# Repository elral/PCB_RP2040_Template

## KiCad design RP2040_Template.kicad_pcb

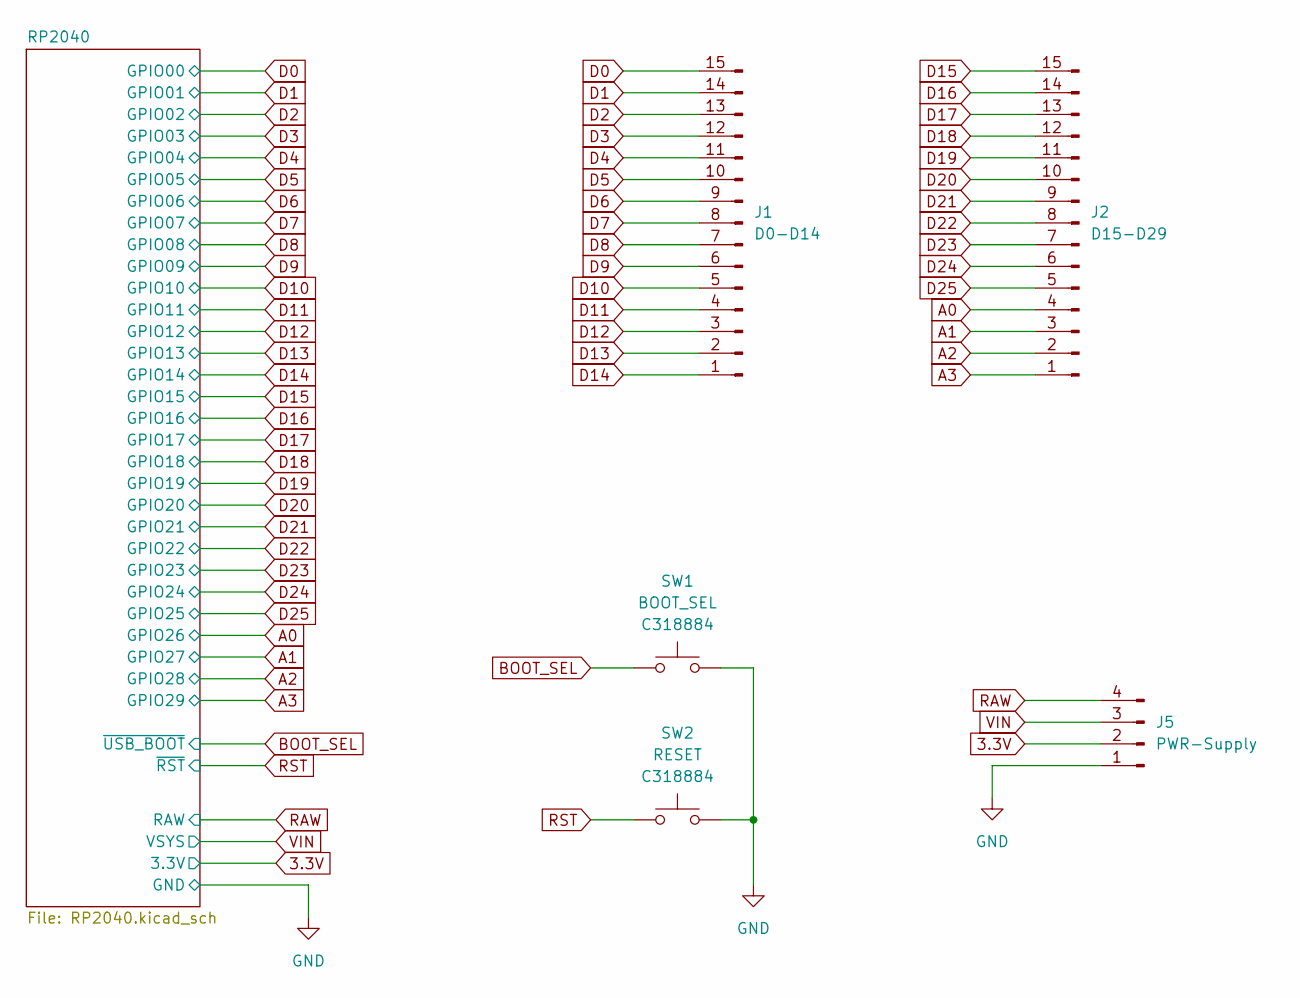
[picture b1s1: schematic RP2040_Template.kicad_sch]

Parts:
J1: D0-D14; PinHeader_1x15_P2.54mm_Vertical
J2: D15-D29; PinHeader_1x15_P2.54mm_Vertical
J5: PWR-Supply; PinHeader_1x04_P2.54mm_Vertical
SW1: BOOT_SEL; SW_Push_1P1T_XKB_TS-1187A; JLCPCB C318884
SW2: RESET; SW_Push_1P1T_XKB_TS-1187A; JLCPCB C318884

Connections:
3.3V: J5.2; also elsewhere on the board
A0: J2.4; also elsewhere on the board
A1: J2.3; also elsewhere on the board
A2: J2.2; also elsewhere on the board
A3: J2.1; also elsewhere on the board
BOOT_SEL: SW1.1; also elsewhere on the board
D0: J1.15; also elsewhere on the board
D1: J1.14; also elsewhere on the board
D2: J1.13; also elsewhere on the board
D3: J1.12; also elsewhere on the board
D4: J1.11; also elsewhere on the board
D5: J1.10; also elsewhere on the board
D6: J1.9; also elsewhere on the board
D7: J1.8; also elsewhere on the board
D8: J1.7; also elsewhere on the board
D9: J1.6; also elsewhere on the board
D10: J1.5; also elsewhere on the board
D11: J1.4; also elsewhere on the board
D12: J1.3; also elsewhere on the board
D13: J1.2; also elsewhere on the board
D14: J1.1; also elsewhere on the board
D15: J2.15; also elsewhere on the board
D16: J2.14; also elsewhere on the board
D17: J2.13; also elsewhere on the board
D18: J2.12; also elsewhere on the board
D19: J2.11; also elsewhere on the board
D20: J2.10; also elsewhere on the board
D21: J2.9; also elsewhere on the board
D22: J2.8; also elsewhere on the board
D23: J2.7; also elsewhere on the board
D24: J2.6; also elsewhere on the board
D25: J2.5; also elsewhere on the board
GND: J5.1, SW1.2, SW2.2; also elsewhere on the board
RAW: J5.4; also elsewhere on the board
RST: SW2.1; also elsewhere on the board
VIN: J5.3; also elsewhere on the board

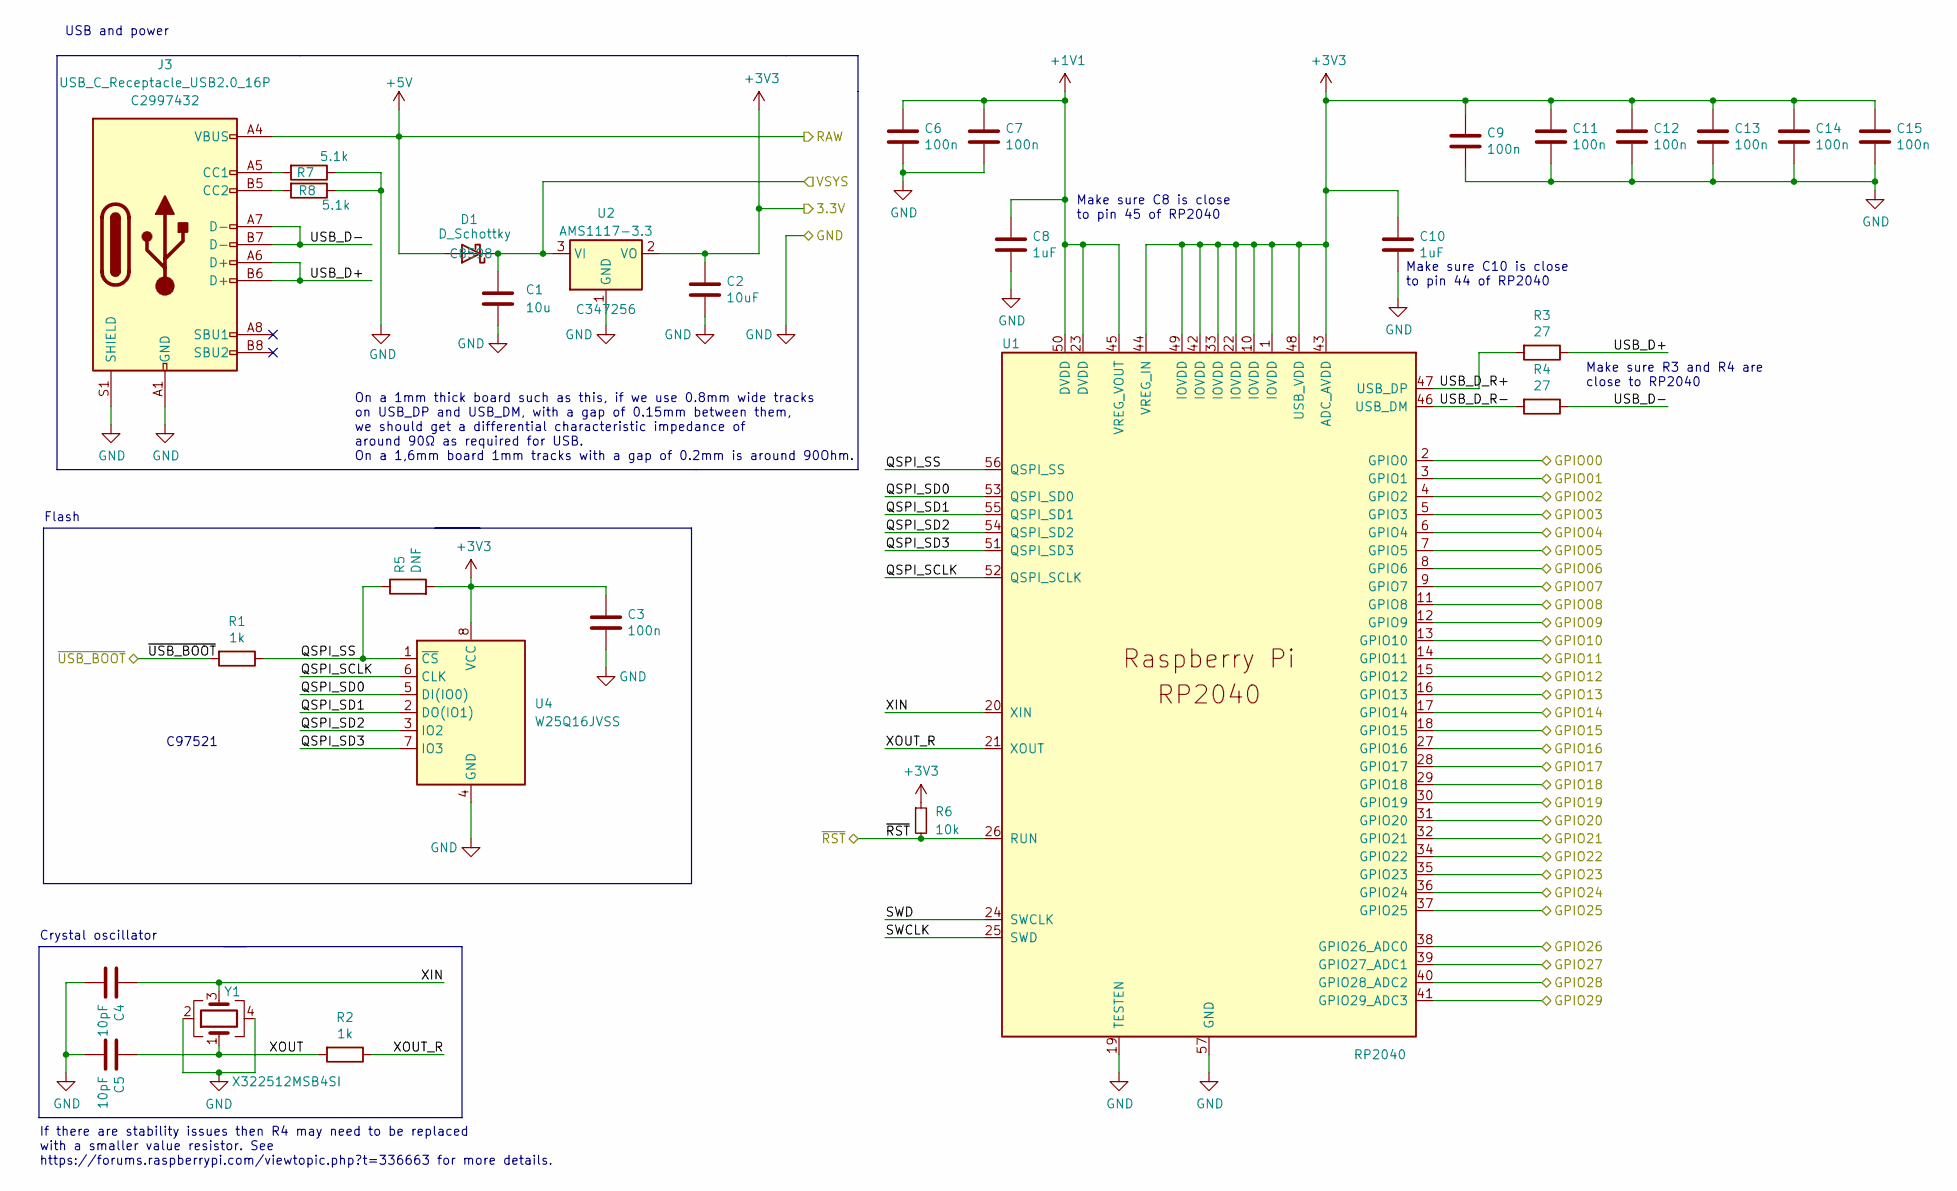
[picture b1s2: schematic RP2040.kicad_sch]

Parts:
C1: 10u; C_0402_1005Metric
C2: 10uF; C_0402_1005Metric; MPN - JLCPCB C52923
C3, C6, C7, C9, C11, C12, C13, C14, C15: 100n; C_0402_1005Metric; MPN - JLCPCB C52923
C4, C5: 10pF; C_0402_1005Metric; MPN - JLCPCB C32949
C8, C10: 1uF; C_0402_1005Metric; MPN - JLCPCB C52923
D1: D_Schottky; D_SOD-123; JLCPCB C8598
J3: USB_C_Receptacle_USB2.0_16P; USB_C_Receptacle_HCTL_HC-TYPE-C-16P-01A; JLCPCB C2997432
R1, R2: 1k; R_0402_1005Metric; MPN - JLCPCB C11702
R3, R4: 27; R_0402_1005Metric; MPN - JLCPCB C25190
R5: DNF; R_0805_2012Metric_Pad1.20x1.40mm_HandSolder
R6: 10k; R_0402_1005Metric; MPN - JLCPCB C25744
R7, R8: 5.1k; R_0402_1005Metric; MPN - JLCPCB C11702
U1: RP2040; QFN56P40_700X700X90L40X18T310N; MPN - JLCPCB C2040
U2: AMS1117-3.3; SOT-223-3_TabPin2; MPN - JLCPCB C6186; JLCPCB C347256
U4: W25Q16JVSS; SOIC-8_5.23x5.23mm_P1.27mm; JLCPCB C2843335
Y1: X322512MSB4SI; Crystal_SMD_3225-4Pin_3.2x2.5mm; MPN - JLCPCB C9002

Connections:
3.3V: C2.1, C3.1, C9.1, C10.1, C11.1, C12.1, C13.1, C14.1, C15.1, R5.2, R6.1, U1.1 (IOVDD), U1.10 (IOVDD), U1.22 (IOVDD), U1.33 (IOVDD), U1.42 (IOVDD), U1.43 (ADC_AVDD), U1.44 (VREG_IN), U1.48 (USB_VDD), U1.49 (IOVDD), U2.2 (VO), U4.8 (VCC); also elsewhere on the board
+1V1: C6.1, C7.1, C8.1, U1.23 (DVDD), U1.45 (VREG_VOUT), U1.50 (DVDD)
/RP2040/QSPI_SCLK: U1.52 (QSPI_SCLK), U4.6 (CLK)
/RP2040/QSPI_SD0: U1.53 (QSPI_SD0), U4.5 (DI(IO0))
/RP2040/QSPI_SD1: U1.55 (QSPI_SD1), U4.2 (DO(IO1))
/RP2040/QSPI_SD2: U1.54 (QSPI_SD2), U4.3 (IO2)
/RP2040/QSPI_SD3: U1.51 (QSPI_SD3), U4.7 (IO3)
/RP2040/QSPI_SS: R1.1, R5.1, U1.56 (QSPI_SS), U4.1 (~CS)
/RP2040/SWCLK: U1.25 (SWD)
/RP2040/SWD: U1.24 (SWCLK)
/RP2040/USB_D+: J3.A6 (D+), J3.B6 (D+), R3.1
/RP2040/USB_D-: J3.A7 (D-), J3.B7 (D-), R4.1
/RP2040/USB_D_R+: R3.2, U1.47 (USB_DP)
/RP2040/USB_D_R-: R4.2, U1.46 (USB_DM)
/RP2040/XIN: C4.1, U1.20 (XIN), Y1.3
/RP2040/XOUT: C5.1, R2.2, Y1.1
/RP2040/XOUT_R: R2.1, U1.21 (XOUT)
A0: U1.38 (GPIO26_ADC0); also elsewhere on the board
A1: U1.39 (GPIO27_ADC1); also elsewhere on the board
A2: U1.40 (GPIO28_ADC2); also elsewhere on the board
A3: U1.41 (GPIO29_ADC3); also elsewhere on the board
BOOT_SEL: R1.2; also elsewhere on the board
D0: U1.2 (GPIO0); also elsewhere on the board
D1: U1.3 (GPIO1); also elsewhere on the board
D2: U1.4 (GPIO2); also elsewhere on the board
D3: U1.5 (GPIO3); also elsewhere on the board
D4: U1.6 (GPIO4); also elsewhere on the board
D5: U1.7 (GPIO5); also elsewhere on the board
D6: U1.8 (GPIO6); also elsewhere on the board
D7: U1.9 (GPIO7); also elsewhere on the board
D8: U1.11 (GPIO8); also elsewhere on the board
D9: U1.12 (GPIO9); also elsewhere on the board
D10: U1.13 (GPIO10); also elsewhere on the board
D11: U1.14 (GPIO11); also elsewhere on the board
D12: U1.15 (GPIO12); also elsewhere on the board
D13: U1.16 (GPIO13); also elsewhere on the board
D14: U1.17 (GPIO14); also elsewhere on the board
D15: U1.18 (GPIO15); also elsewhere on the board
D16: U1.27 (GPIO16); also elsewhere on the board
D17: U1.28 (GPIO17); also elsewhere on the board
D18: U1.29 (GPIO18); also elsewhere on the board
D19: U1.30 (GPIO19); also elsewhere on the board
D20: U1.31 (GPIO20); also elsewhere on the board
D21: U1.32 (GPIO21); also elsewhere on the board
D22: U1.34 (GPIO22); also elsewhere on the board
D23: U1.35 (GPIO23); also elsewhere on the board
D24: U1.36 (GPIO24); also elsewhere on the board
D25: U1.37 (GPIO25); also elsewhere on the board
GND: C1.2, C2.2, C3.2, C4.2, C5.2, C6.2, C7.2, C8.2, C9.2, C10.2, C11.2, C12.2, C13.2, C14.2, C15.2, J3.A1 (GND), J3.A12 (GND), J3.B1 (GND), J3.B12 (GND), J3.S1 (SHIELD), R7.1, R8.1, U1.19 (TESTEN), U1.57 (GND), U2.1 (GND), U4.4 (GND), Y1.2, Y1.4; also elsewhere on the board
unnamed: J3.A5 (CC1), R7.2
unnamed: J3.B5 (CC2), R8.2
RAW: D1.2 (A), J3.A4 (VBUS), J3.A9 (VBUS), J3.B4 (VBUS), J3.B9 (VBUS); also elsewhere on the board
RST: R6.2, U1.26 (RUN); also elsewhere on the board
VIN: C1.1, D1.1 (K), U2.3 (VI); also elsewhere on the board

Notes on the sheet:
Make sure C8 is close to pin 45 of RP2040
USB and power
Make sure C10 is close to pin 44 of RP2040
Make sure R3 and R4 are close to RP2040
C97521
If there are stability issues then R4 may need to be replaced with a smaller value resistor. See https://forums.raspberrypi.com/viewtopic.php?t=336663 for more details.
On a 1mm thick board such as this, if we use 0.8mm wide tracks on USB_DP and USB_DM, with a gap of 0.15mm between them, we should get a differential characteristic impedance of around 90Ω as required for USB. On a 1,6mm board 1mm tracks with a gap of 0.2mm is around 90Ohm.
Flash
Crystal oscillator

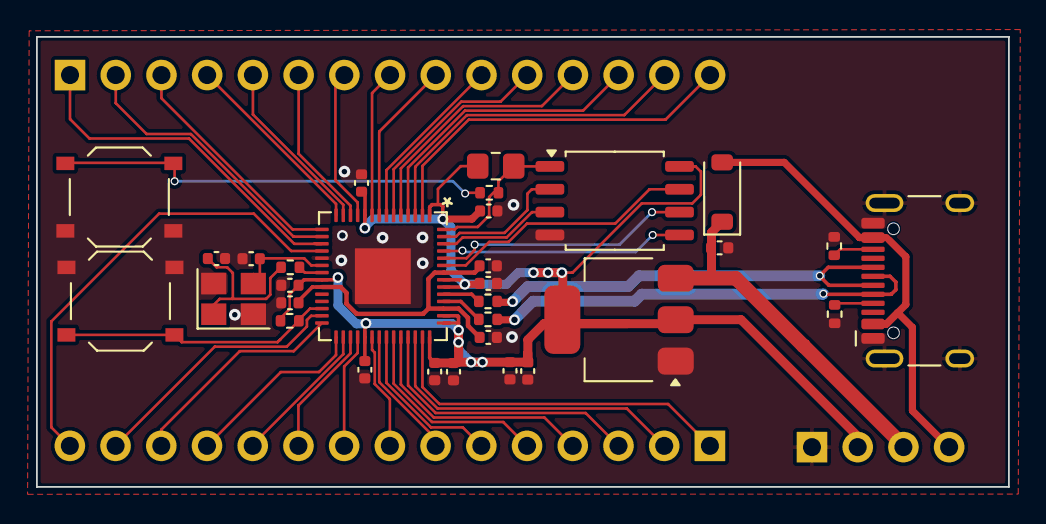
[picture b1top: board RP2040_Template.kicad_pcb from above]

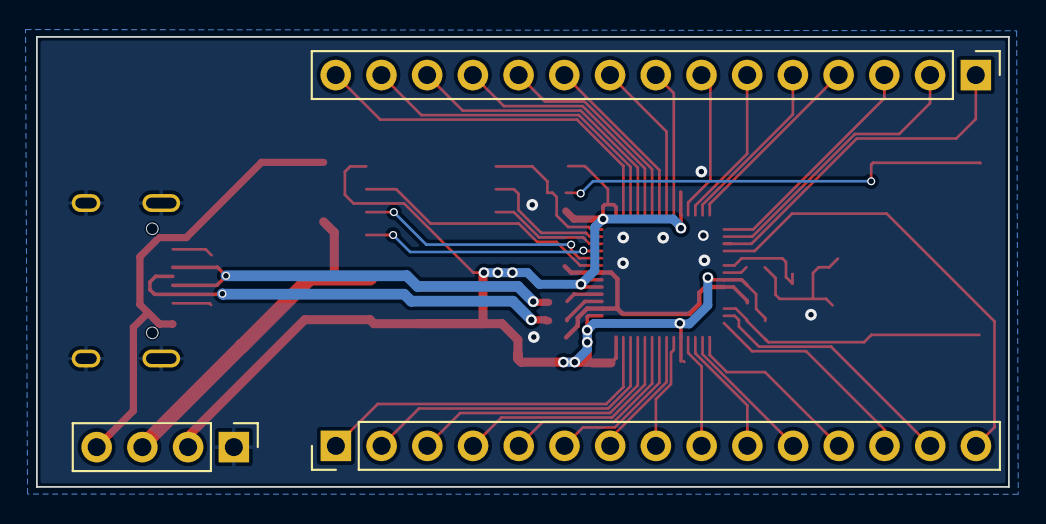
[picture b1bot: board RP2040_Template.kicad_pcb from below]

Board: 2 copper layers, 54.0 x 25.0 mm, 34 parts (3 on the bottom side), 52 nets.

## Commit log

2025-05-24 exclude KiCad auto generated files
2025-08-12 Update to KiCad Version 9
